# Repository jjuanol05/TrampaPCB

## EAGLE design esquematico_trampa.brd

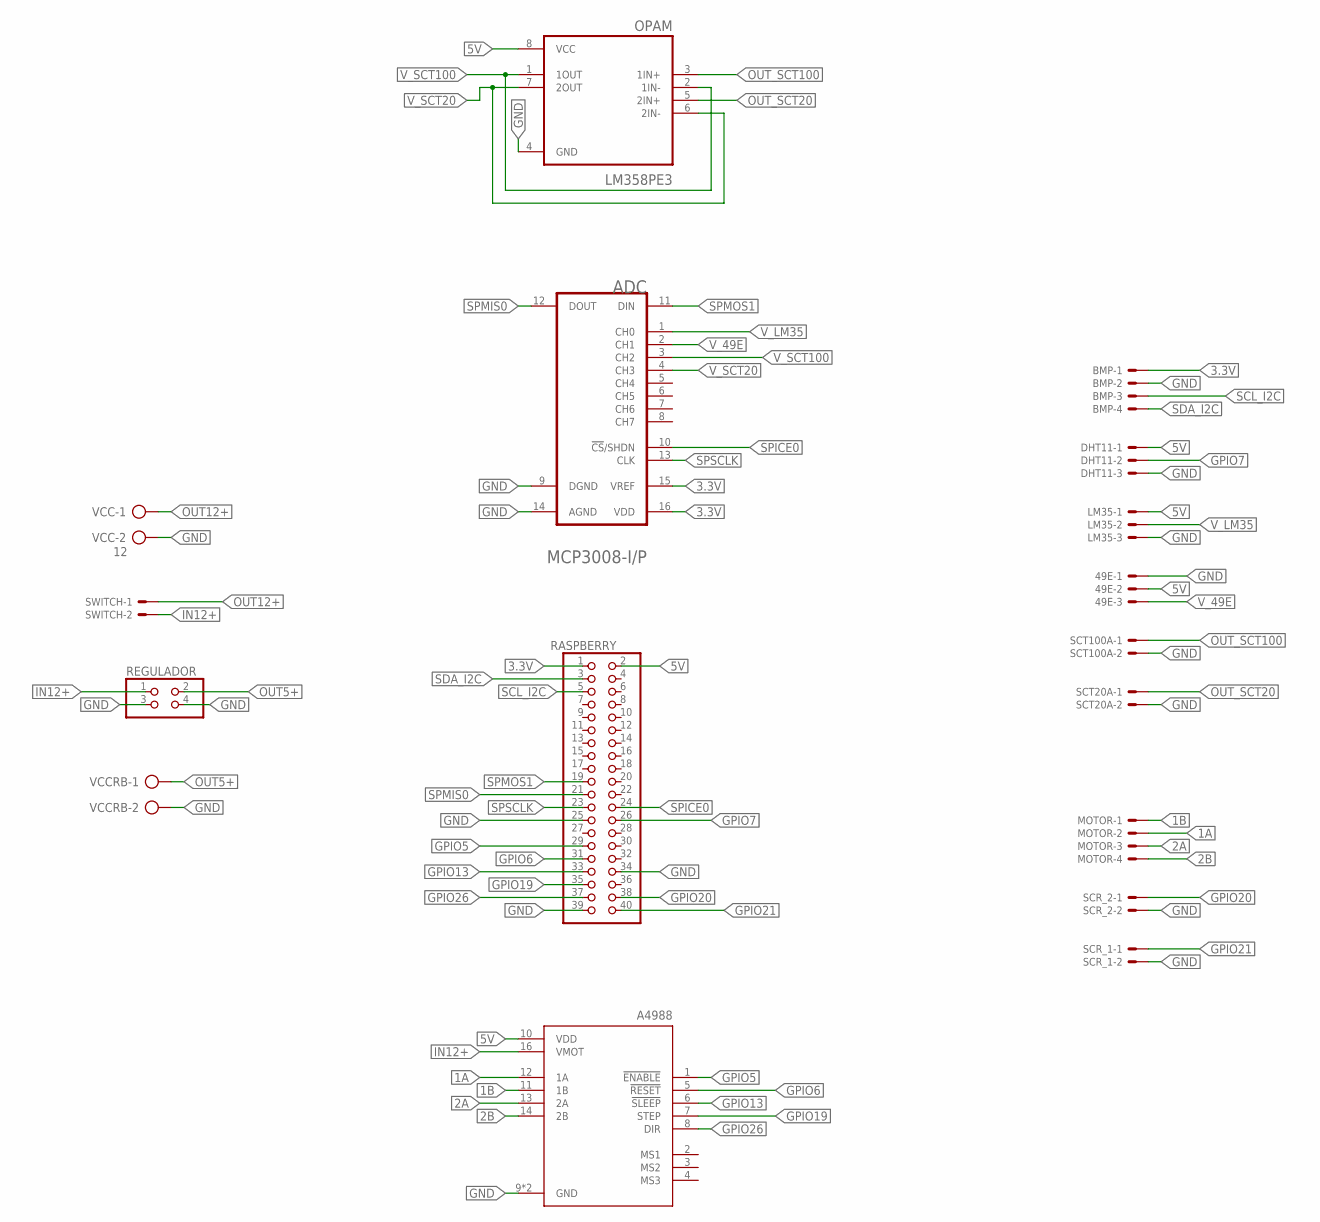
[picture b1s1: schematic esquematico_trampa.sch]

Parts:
49E: 22-23-2031
A4988: A4988_STEPPER_MOTOR_DRIVER_CARRIER; MODULE_A4988_STEPPER_MOTOR_DRIVER_CARRIER
ADC: MICROCHIP_MCP3008-I-PMICROCHIP_MCP3008-I-P_0_0; MICROCHIP_MCP3008-I-P_0
BMP: 22-23-2041
DHT11: 22-23-2031
LM35: 22-23-2031
MOTOR: 22-23-2041
OPAM: LM358PE3; DIP794W45P254L959H508Q8
RASPBERRY: PINHD-2X20; 2X20
REGULADOR: PINHD-2X2; 2X02
SCR_1, SCR_2: 22-23-2021
SCT20A, SCT100A: 22-23-2021
SWITCH: 22-23-2021
VCC: 12; AK500/2-H
VCCRB: AK500/2-H

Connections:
1A: A4988.12 (1A), MOTOR.2
1B: A4988.11 (1B), MOTOR.1
2A: A4988.13 (2A), MOTOR.3
2B: A4988.14 (2B), MOTOR.4
3.3V: ADC.15 (VREF), ADC.16 (VDD), BMP.1, RASPBERRY.1
5V: 49E.2, A4988.10 (VDD), DHT11.1, LM35.1, OPAM.8 (VCC), RASPBERRY.2
GND: 49E.1, A4988.9 (GND), A4988.15 (GND), ADC.9 (DGND), ADC.14 (AGND), BMP.2, DHT11.3, LM35.3, OPAM.4 (GND), RASPBERRY.25, RASPBERRY.34, RASPBERRY.39, REGULADOR.3, REGULADOR.4, SCR_1.2, SCR_2.2, SCT20A.2, SCT100A.2, VCC.2, VCCRB.2
GPIO5: A4988.1 (!ENABLE), RASPBERRY.29
GPIO6: A4988.5 (!RESET), RASPBERRY.31
GPIO7: DHT11.2, RASPBERRY.26
GPIO13: A4988.6 (!SLEEP), RASPBERRY.33
GPIO19: A4988.7 (STEP), RASPBERRY.35
GPIO20: RASPBERRY.38, SCR_2.1
GPIO21: RASPBERRY.40, SCR_1.1
GPIO26: A4988.8 (DIR), RASPBERRY.37
IN12+: A4988.16 (VMOT), REGULADOR.1, SWITCH.2
OUT5+: REGULADOR.2, VCCRB.1
OUT12+: SWITCH.1, VCC.1
OUT_SCT20: OPAM.5 (2IN+), SCT20A.1
OUT_SCT100: OPAM.3 (1IN+), SCT100A.1
SCL_I2C: BMP.3, RASPBERRY.5
SDA_I2C: BMP.4, RASPBERRY.3
SPICE0: ADC.10 (!CS!/SHDN), RASPBERRY.24
SPMIS0: ADC.12 (DOUT), RASPBERRY.21
SPMOS1: ADC.11 (DIN), RASPBERRY.19
SPSCLK: ADC.13 (CLK), RASPBERRY.23
V_49E: 49E.3, ADC.2 (CH1)
V_LM35: ADC.1 (CH0), LM35.2
V_SCT20: ADC.4 (CH3), OPAM.6 (2IN-), OPAM.7 (2OUT)
V_SCT100: ADC.3 (CH2), OPAM.1 (1OUT), OPAM.2 (1IN-)

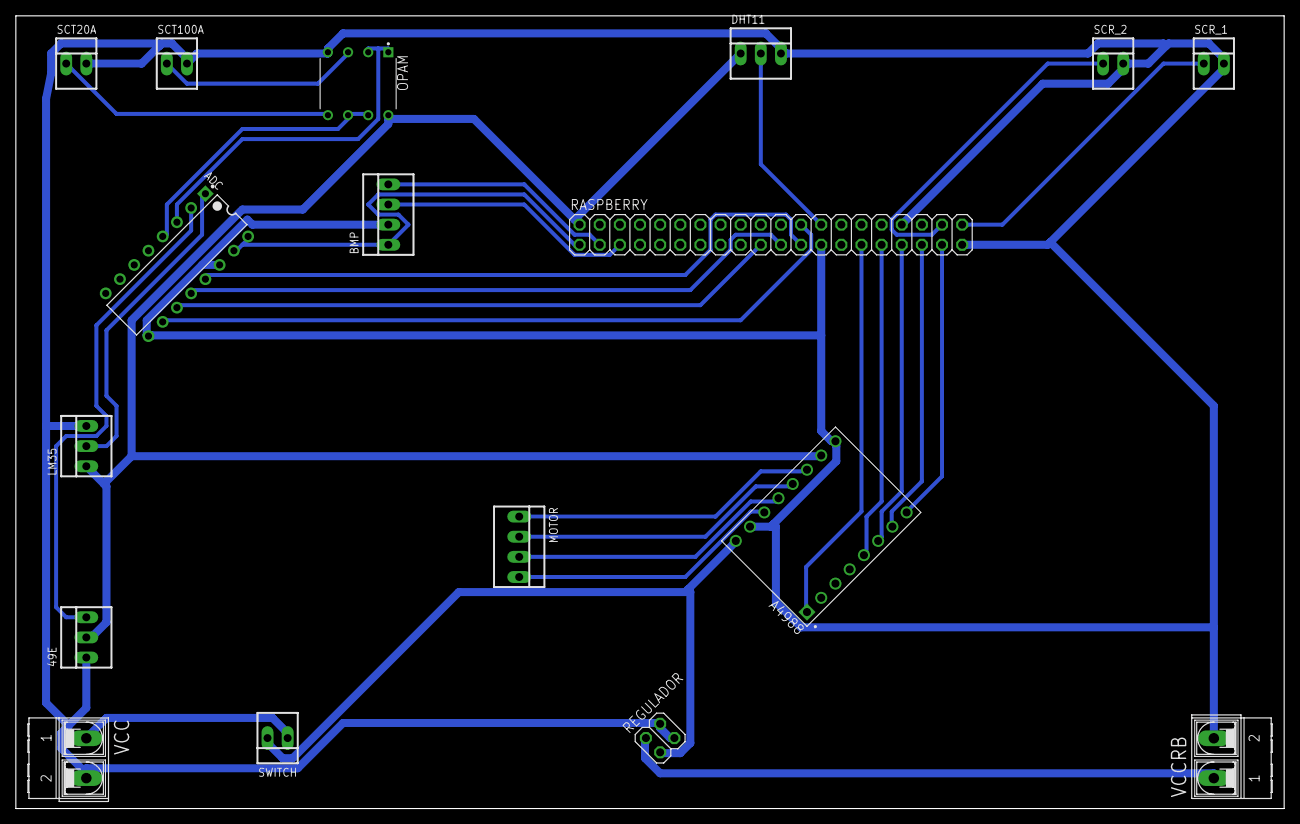
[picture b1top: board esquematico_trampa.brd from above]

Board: 2 copper layers, 160.0 x 100.0 mm, 17 parts (0 on the bottom side), 30 nets.

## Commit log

2022-11-16 Esquematico completo
2022-11-16 Archvos ignorados
2022-11-16 Nombre todas las pistas dependiendo su conexión
2022-11-16 Board de la trampa
2022-11-17 Esquemático más optimizado
2022-11-17 Diseño erroneo
2022-11-17 Renombre todas las conexiones
2022-11-20 agregue labels para evitar desorden en las conexiones
2022-11-20 vista del esquematico
2022-11-20 agregue archivo gitignore
2022-11-20 agregue archivos para ignorar
2022-11-20 agregue archivo de routeo
2022-11-20 diseño 90% de routeo
2022-11-20 esquematico con cambios en gpio7
2022-11-20 agregue archivo pro
2022-11-22 ordene todos los componentes
2022-11-22 ruteo pre-eliminar
2022-11-22 agregue archivos caché
2022-11-22 conecte el vmotor a 12v
2022-11-22 esquematico ordenado y board 100 ruteado
2022-11-22 imagenes del esquematico y el board
2022-11-22 agregue pdf's para impresion en placa de cobre
2022-11-22 agregue archivos de documentacion
2022-11-22 eliminando archivos ctl
